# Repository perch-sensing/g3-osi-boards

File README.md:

# Perch 3GRMC Platform

## Getting Started

You'll want to clone this repo with an `ssh` key. To setup an `ssh` key on
GitHub, follow this [link](https://docs.github.com/en/github/authenticating-to-github/connecting-to-github-with-ssh).

Additionally, this README assumes that you are using Visual Studio Code.

### HW/SW

You need to initialize the various submodules with the following command:

```shell
git submodule update --init --recursive
```

The submodules include the Perch kicad library as well as micropython libraries.

### Hardware

The hardware is designed using KiCad 5.X. You will need to download KiCad from
[https://kicad.org/download/](https://kicad.org/download/).

To work with KiCad files in a Git repository, certain parts of the file should
be ignored. To ignore these commands in git, you can add to the project-local
config. To facilitate this, a `.gitconfig` file has been provided in this
repository. To use the provided `.gitconfig` file, you need to add it to the
project config.

Run the following command:

```shell
git config --local include.path ../.gitconfig
```

Next, you'll want to install `plotkicadsch` to your path. You can download
the binary [here](https://github.com/jnavila/plotkicadsch/releases). For
assistance in adding a folder to your path, visit
[this](https://www.howtogeek.com/118594/how-to-edit-your-system-path-for-easy-command-line-access/) link.

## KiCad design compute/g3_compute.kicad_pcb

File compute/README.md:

Here is a link to the Compute BOM:
https://docs.google.com/spreadsheets/d/1j4ZL0j2LjKp-IoZsxxflOpX7Q5H--Hl_RDHMVLFPHzU/edit#gid=0

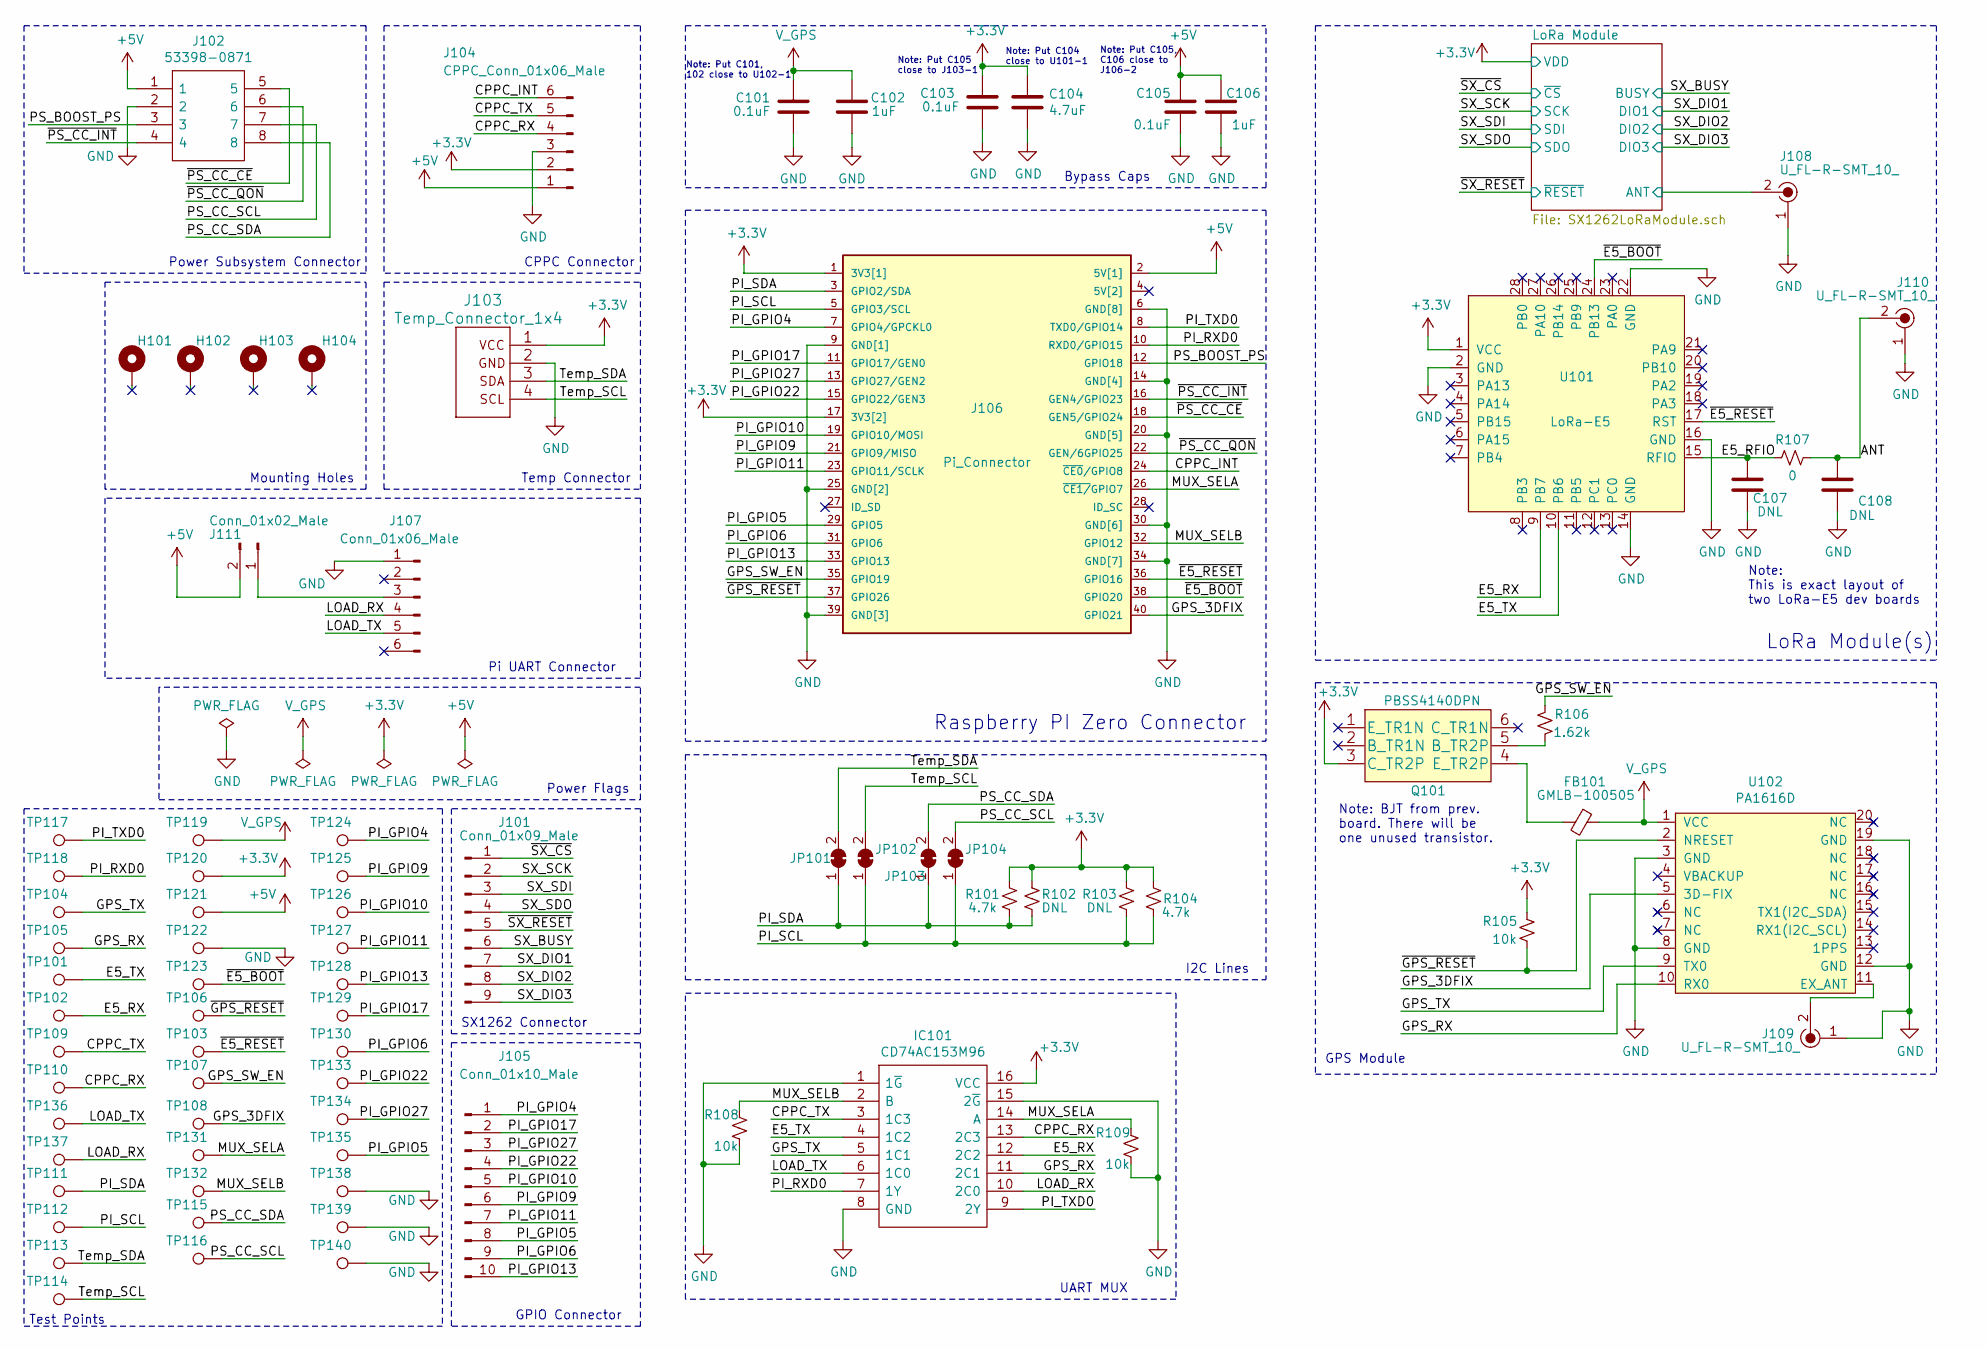
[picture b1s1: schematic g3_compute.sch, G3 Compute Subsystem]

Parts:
C101, C103, C105: 0.1uF; C_0402_1005Metric_Pad0.74x0.62mm_HandSolder
C102, C106: 1uF; C_0402_1005Metric_Pad0.74x0.62mm_HandSolder
C104: 4.7uF; C_0402_1005Metric_Pad0.74x0.62mm_HandSolder
C107, C108: DNL; C_0402_1005Metric_Pad0.74x0.62mm_HandSolder
FB101: GMLB-100505; R_0402_1005Metric_Pad0.72x0.64mm_HandSolder
H101, H102, H103, H104: MountingHole_Pad; MountingHole_2.5mm_Pad
IC101: CD74AC153M96; SOIC127P600X175-16N_MUX; Mouser Part Number 595-CD74AC153M96
J101: Conn_01x09_Male; PinHeader_1x09_P2.54mm_Vertical
J102: 53398-0871; 53398-0871_Molex
J103: Temp_Connector_1x4; 1702474_Temp_Sensor_Connector
J104: CPPC_Conn_01x06_Male; PinHeader_1x06_P2.54mm_Vertical_SMD_Pin1Left
J105: Conn_01x10_Male; PinHeader_1x10_P2.54mm_Vertical
J106: Pi_Connector; ADA3708_RaspPiZero; Manufacturer_Part_Number 2885
J107: Conn_01x06_Male; PinHeader_1x06_P2.54mm_Vertical
J108, J109, J110: U_FL-R-SMT_10_; Coax_Conn_U.FL; MPN U.FL-R-SMT(10); Digi-Key_PN H9161CT-ND
J111: Conn_01x02_Male; PinHeader_1x02_P2.54mm_Vertical_SMD_Pin1Left
JP101, JP102, JP103, JP104: SolderJumper_2_Bridged; SolderJumper-2_P1.3mm_Bridged_RoundedPad1.0x1.5mm
Q101: PBSS4140DPN
R101, R104: 4.7k; R_0402_1005Metric_Pad0.72x0.64mm_HandSolder
R102, R103: DNL; R_0402_1005Metric_Pad0.72x0.64mm_HandSolder
R105, R108, R109: 10k; R_0402_1005Metric_Pad0.72x0.64mm_HandSolder
R106: 1.62k; R_0603_1608Metric_Pad0.98x0.95mm_HandSolder
R107: 0; R_0402_1005Metric_Pad0.72x0.64mm_HandSolder
TP101, TP102, TP103, TP104, TP105, TP106, TP107, TP108, TP109, TP110, TP111, TP112, TP113, TP114, TP115, TP116, TP117, TP118, TP119, TP120, TP121, TP122, TP123, TP124, TP125, TP126, TP127, TP128, TP129, TP130, TP131, TP132, TP133, TP134, TP135, TP136, TP137, TP138, TP139, TP140: TestPoint; HARWIN_S2751-46R
U101: LoRa-E5
U102: PA1616D; PA1616D_GPS

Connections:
+3V3: C103.2, C104.1, IC101.16 (VCC), J103.1 (Vdd), J104.2, J106.1 (3V3[1]), J106.17 (3V3[2]), Q101.3 (C_TR2P), R101.2, R102.2, R103.2, R104.2, R105.2, TP120.1, U101.1 (VCC); also elsewhere on the board
+5V: C105.2, C106.2, J102.1, J104.1, J106.2 (5V[1]), J111.2, TP121.1
/ANT: C108.1, J110.2, R107.2
/CPPC_INT: J104.6, J106.24 (~CE0~/GPIO8)
/CPPC_RX: IC101.13 (2C3), J104.4, TP110.1
/CPPC_TX: IC101.3 (1C3), J104.5, TP109.1
/E5_RFIO: C107.1, R107.1, U101.15 (RFIO)
/E5_RX: IC101.12 (2C2), TP102.1, U101.9 (PB7)
/E5_TX: IC101.4 (1C2), TP101.1, U101.10 (PB6)
/GPS_3DFIX: J106.40 (GPIO21), TP108.1, U102.5 (3D-FIX)
/GPS_RX: IC101.11 (2C1), TP105.1, U102.10 (RX0)
/GPS_SW_EN: J106.35 (GPIO19), R106.2, TP107.1
/GPS_TX: IC101.5 (1C1), TP104.1, U102.9 (TX0)
/LOAD_RX: IC101.10 (2C0), J107.4, TP137.1
/LOAD_TX: IC101.6 (1C0), J107.5, TP136.1
/LoRa Module/ANT: J108.2; also elsewhere on the board
/MUX_SELA: IC101.14 (A), J106.26 (~CE1/~GPIO7), R109.2, TP131.1
/MUX_SELB: IC101.2 (B), J106.32 (GPIO12), R108.2, TP132.1
/PI_GPIO4: J105.1, J106.7 (GPIO4/GPCKL0), TP124.1
/PI_GPIO5: J105.8, J106.29 (GPIO5), TP135.1
/PI_GPIO6: J105.9, J106.31 (GPIO6), TP130.1
/PI_GPIO9: J105.6, J106.21 (GPIO9/MISO), TP125.1
/PI_GPIO10: J105.5, J106.19 (GPIO10/MOSI), TP126.1
/PI_GPIO11: J105.7, J106.23 (GPIO11/SCLK), TP127.1
/PI_GPIO13: J105.10, J106.33 (GPIO13), TP128.1
/PI_GPIO17: J105.2, J106.11 (GPIO17/GEN0), TP129.1
/PI_GPIO22: J105.4, J106.15 (GPIO22/GEN3), TP133.1
/PI_GPIO27: J105.3, J106.13 (GPIO27/GEN2), TP134.1
/PI_RXD0: IC101.7 (1Y), J106.10 (RXD0/GPIO15), TP118.1
/PI_SCL: J106.5 (GPIO3/SCL), JP102.1 (A), JP104.1 (A), R103.1, R104.1, TP112.1
/PI_SDA: J106.3 (GPIO2/SDA), JP101.1 (A), JP103.1 (A), R101.1, R102.1, TP111.1
/PI_TXD0: IC101.9 (2Y), J106.8 (TXD0/GPIO14), TP117.1
/PS_BOOST_PS: J102.3, J106.12 (GPIO18)
/PS_CC_SCL: J102.7, JP104.2 (B), TP116.1
/PS_CC_SDA: J102.8, JP103.2 (B), TP115.1
/SX_BUSY: J101.6; also elsewhere on the board
/SX_DIO1: J101.7; also elsewhere on the board
/SX_DIO2: J101.8; also elsewhere on the board
/SX_DIO3: J101.9; also elsewhere on the board
/SX_SCK: J101.2; also elsewhere on the board
/SX_SDI: J101.3; also elsewhere on the board
/SX_SDO: J101.4; also elsewhere on the board
/Temp_SCL: J103.4 (SCL), JP102.2 (B), TP114.1
/Temp_SDA: J103.3 (SDA), JP101.2 (B), TP113.1
/~E5_BOOT: J106.38 (GPIO20), TP123.1, U101.24 (PB13~)
/~E5_RESET: J106.36 (GPIO16), TP103.1, U101.17 (RST)
/~GPS_RESET: J106.37 (GPIO26), R105.1, TP106.1, U102.2 (NRESET)
/~PS_CC_CE: J102.5, J106.18 (GEN5/GPIO24)
/~PS_CC_INT: J102.4, J106.16 (GEN4/GPIO23)
/~PS_CC_QON: J102.6, J106.22 (GEN/6GPIO25)
/~SX_CS: J101.1; also elsewhere on the board
/~SX_RESET: J101.5; also elsewhere on the board
GND: C101.1, C102.1, C103.1, C104.2, C105.1, C106.1, C107.2, C108.2, IC101.1 (1~G), IC101.8 (GND), IC101.15 (2~G), J102.2, J103.2 (Gnd), J104.3, J106.6 (GND[8]), J106.9 (GND[1]), J106.14 (GND[4]), J106.20 (GND[5]), J106.25 (GND[2]), J106.30 (GND[6]), J106.34 (GND[7]), J106.39 (GND[3]), J107.1, J108.1, J109.1, J110.1, R108.1, R109.1, TP122.1, TP138.1, TP139.1, TP140.1, U101.2 (GND), U101.14 (GND), U101.16 (GND), U101.22 (GND), U102.3 (GND), U102.8 (GND), U102.12 (GND), U102.19 (GND); also elsewhere on the board
unnamed: FB101.2, Q101.4 (E_TR2P)
unnamed: J107.3, J111.1
unnamed: J109.2, U102.11 (EX_ANT)
unnamed: Q101.5 (B_TR2P), R106.1
V_GPS: C101.2, C102.2, FB101.1, TP119.1, U102.1 (VCC)

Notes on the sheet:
Power Subsystem Connector
Mounting Holes
SX1262 Connector
GPIO Connector
GPS Module
Note: BJT from prev. board. There will be one unused transistor.
Note: This is exact layout of two LoRa-E5 dev boards
Note: Put C101, 102 close to U102-1
Note: Put C105 close to J103-1
Pi UART Connector
Note: Put C105, C106 close to J106-2
Bypass Caps
Raspberry PI Zero Connector
LoRa Module(s)
Temp Connector
CPPC Connector
I2C Lines
Test Points
UART MUX
Power Flags
Note: Put C104 close to U101-1

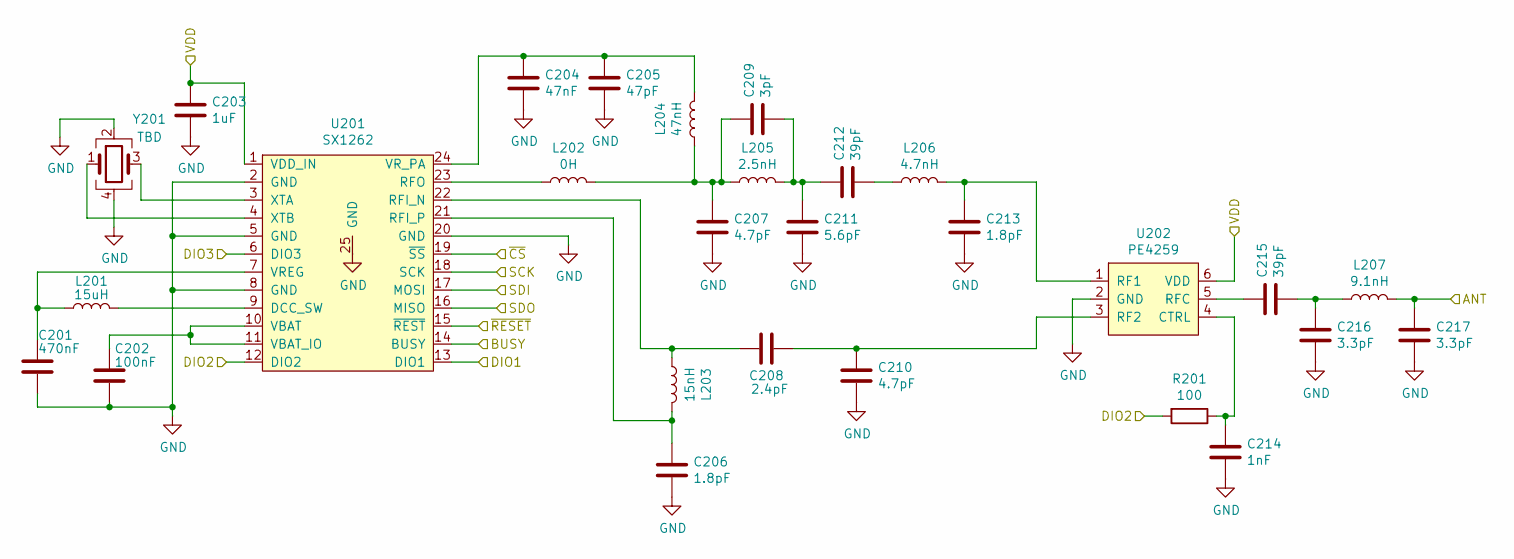
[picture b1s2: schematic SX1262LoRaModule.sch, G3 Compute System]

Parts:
C201: 470nF; C_0402_1005Metric_Pad0.74x0.62mm_HandSolder
C202: 100nF; C_0402_1005Metric_Pad0.74x0.62mm_HandSolder
C203: 1uF; C_0402_1005Metric_Pad0.74x0.62mm_HandSolder
C204: 47nF; C_0402_1005Metric_Pad0.74x0.62mm_HandSolder
C205: 47pF; C_0402_1005Metric_Pad0.74x0.62mm_HandSolder
C206, C213: 1.8pF; C_0402_1005Metric_Pad0.74x0.62mm_HandSolder
C207, C210: 4.7pF; C_0402_1005Metric_Pad0.74x0.62mm_HandSolder
C208: 2.4pF; C_0402_1005Metric_Pad0.74x0.62mm_HandSolder
C209: 3pF; C_0402_1005Metric_Pad0.74x0.62mm_HandSolder
C211: 5.6pF; C_0402_1005Metric_Pad0.74x0.62mm_HandSolder
C212, C215: 39pF; C_0402_1005Metric_Pad0.74x0.62mm_HandSolder
C214: 1nF; C_0402_1005Metric_Pad0.74x0.62mm_HandSolder
C216, C217: 3.3pF; C_0402_1005Metric_Pad0.74x0.62mm_HandSolder
L201: 15uH; L_0805_2012Metric_Pad1.05x1.20mm_HandSolder
L202: 0H; L_0402_1005Metric_Pad0.77x0.64mm_HandSolder
L203: 15nH; L_0402_1005Metric_Pad0.77x0.64mm_HandSolder
L204: 47nH; L_0402_1005Metric_Pad0.77x0.64mm_HandSolder
L205: 2.5nH; L_0402_1005Metric_Pad0.77x0.64mm_HandSolder
L206: 4.7nH; L_0402_1005Metric_Pad0.77x0.64mm_HandSolder
L207: 9.1nH; L_0402_1005Metric_Pad0.77x0.64mm_HandSolder
R201: 100; R_0402_1005Metric_Pad0.72x0.64mm_HandSolder
U201: SX1262; QFN-24-1EP_4x4mm_P0.5mm_EP2.7x2.7mm
U202: PE4259; SOT-363_SC-70-6
Y201: TBD; Crystal_SMD_2016-4Pin_2.0x1.6mm

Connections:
+3V3: C203.1, U201.1 (VDD_IN), U202.6 (VDD); also elsewhere on the board
/LoRa Module/ANT: C217.1, L207.2; also elsewhere on the board
/SX_BUSY: U201.14 (BUSY); also elsewhere on the board
/SX_DIO1: U201.13 (DIO1); also elsewhere on the board
/SX_DIO2: R201.2, U201.12 (DIO2); also elsewhere on the board
/SX_DIO3: U201.6 (DIO3); also elsewhere on the board
/SX_SCK: U201.18 (SCK); also elsewhere on the board
/SX_SDI: U201.17 (MOSI); also elsewhere on the board
/SX_SDO: U201.16 (MISO); also elsewhere on the board
/~SX_CS: U201.19 (~SS); also elsewhere on the board
/~SX_RESET: U201.15 (~REST); also elsewhere on the board
GND: C201.2, C202.2, C203.2, C204.2, C205.2, C206.2, C207.2, C210.2, C211.2, C213.2, C214.2, C216.2, C217.2, U201.2 (GND), U201.5 (GND), U201.8 (GND), U201.20 (GND), U201.25 (GND), U202.2 (GND), Y201.2, Y201.4; also elsewhere on the board
unnamed: C201.1, L201.1, U201.7 (VREG)
unnamed: C202.1, U201.10 (VBAT), U201.11 (VBAT_IO)
unnamed: C204.1, C205.1, L204.2, U201.24 (VR_PA)
unnamed: C206.1, L203.2, U201.21 (RFI_P)
unnamed: C207.1, C209.1, L202.2, L204.1, L205.1
unnamed: C208.1, L203.1, U201.22 (RFI_N)
unnamed: C208.2, C210.1, U202.3 (RF2)
unnamed: C209.2, C211.1, C212.1, L205.2
unnamed: C212.2, L206.1
unnamed: C213.1, L206.2, U202.1 (RF1)
unnamed: C214.1, R201.1, U202.4 (CTRL)
unnamed: C215.1, U202.5 (RFC)
unnamed: C215.2, C216.1, L207.1
unnamed: L201.2, U201.9 (DCC_SW)
unnamed: L202.1, U201.23 (RFO)
unnamed: U201.3 (XTA), Y201.3
unnamed: U201.4 (XTB), Y201.1

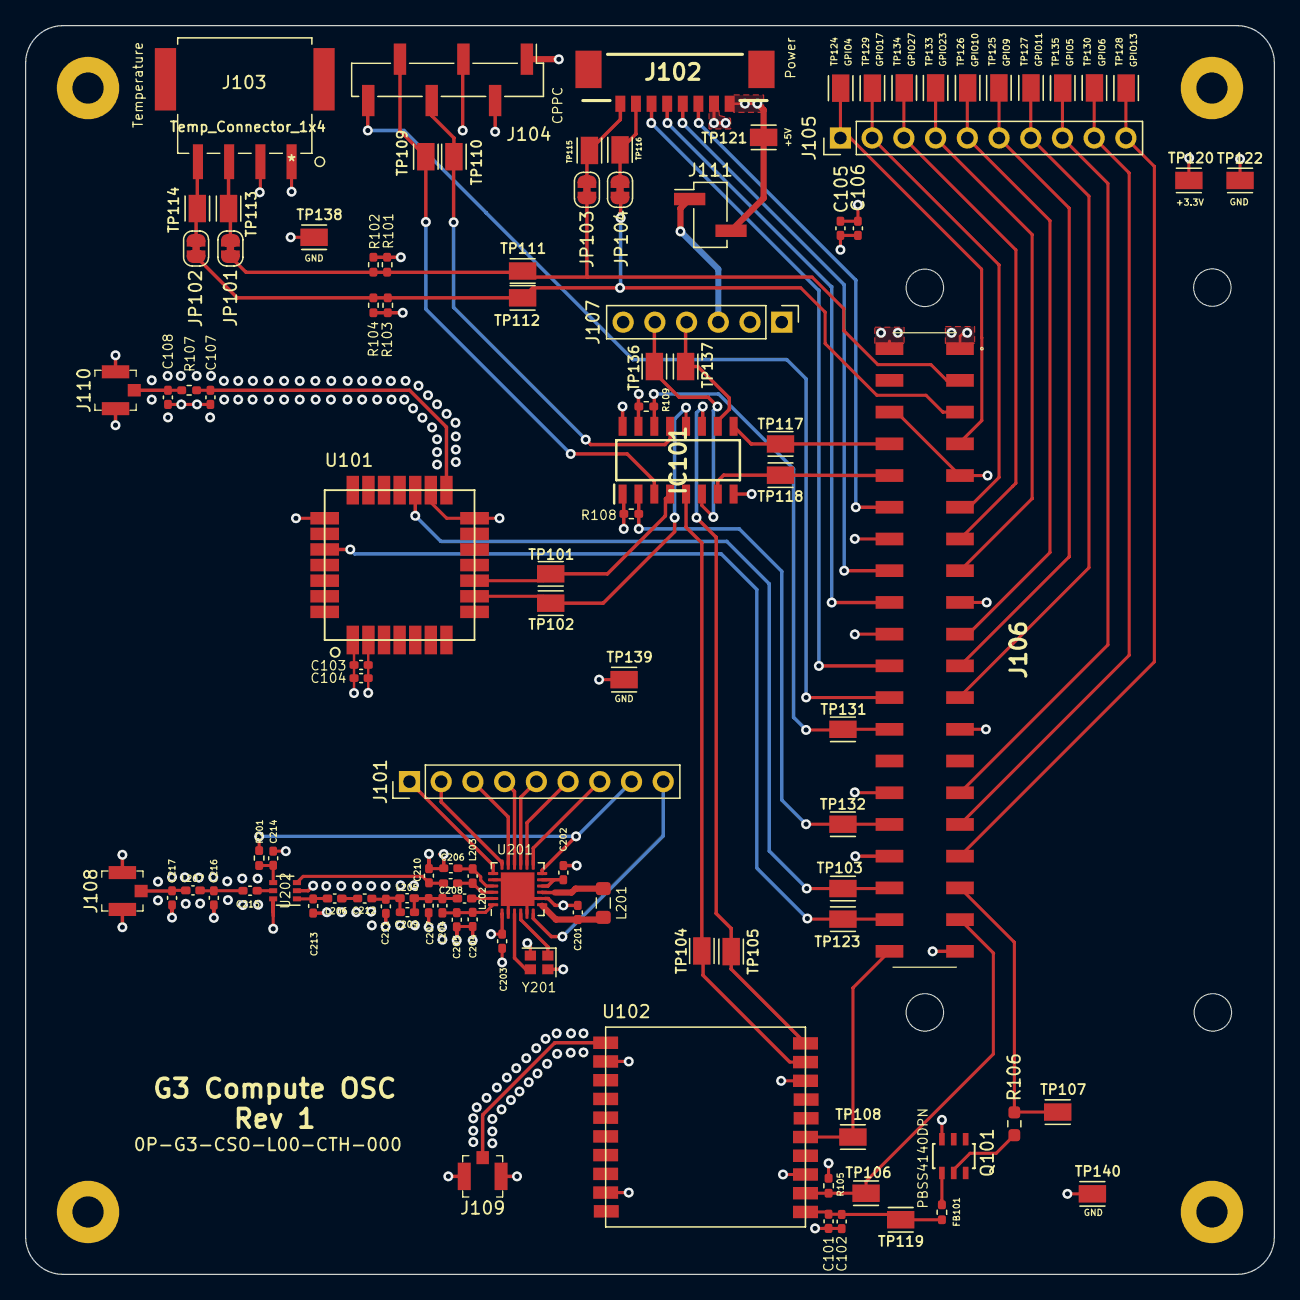
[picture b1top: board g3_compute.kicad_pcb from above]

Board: 4 copper layers, 100.0 x 100.0 mm, 109 parts (0 on the bottom side), 75 nets.

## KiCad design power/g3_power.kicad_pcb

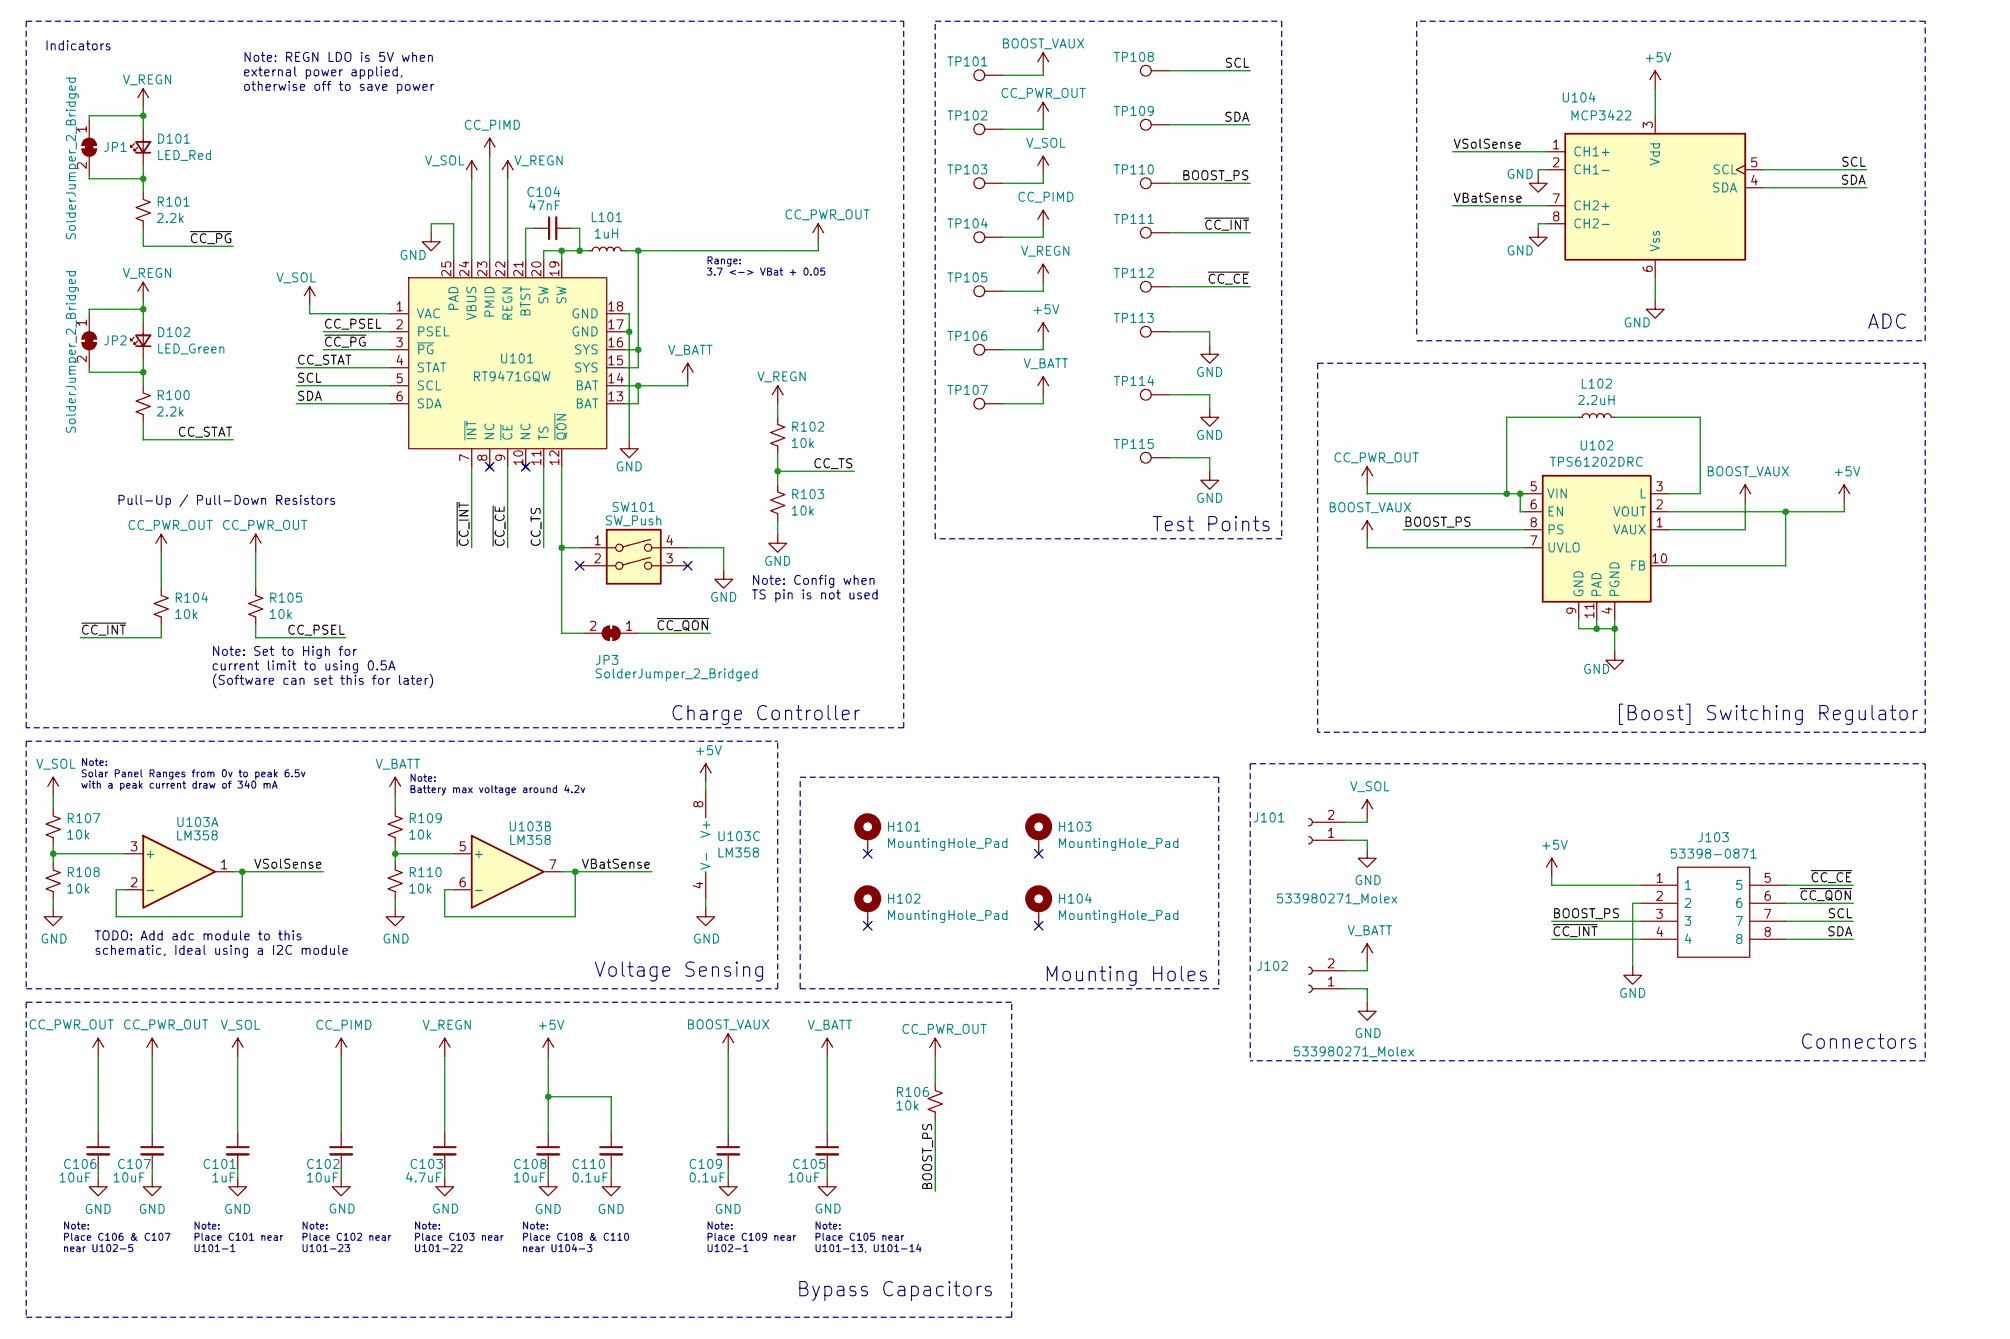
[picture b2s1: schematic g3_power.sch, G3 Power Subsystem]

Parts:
C101: 1uF; C_0402_1005Metric_Pad0.74x0.62mm_HandSolder; Manufacturer_Part_Number CC0402MRX5R6BB105
C102, C105, C106, C107, C108: 10uF; C_0402_1005Metric_Pad0.74x0.62mm_HandSolder; Manufacturer_Part_Number CAP CER 10000PF 16V X7R 0402
C103: 4.7uF; C_0402_1005Metric_Pad0.74x0.62mm_HandSolder; Manufacturer_Part_Number CC0402MRX5R6BB475
C104: 47nF; C_0805_2012Metric_Pad1.18x1.45mm_HandSolder; Manufacturer_Part_Number CL21B473KCCWPNC
C109, C110: 0.1uF; C_0402_1005Metric_Pad0.74x0.62mm_HandSolder; Manufacturer_Part_Number CC0402JRX7R7BB104
D101: LED_Red; LED_0402_1005Metric_Pad0.77x0.64mm_HandSolder; Manufacturer_Part_Number SML-LX0402SIC-TR
D102: LED_Green; LED_0402_1005Metric_Pad0.77x0.64mm_HandSolder; Manufacturer_Part_Number SML-LX0402SUGC-TR
H101, H102, H103, H104: MountingHole_Pad; MountingHole_2.5mm_Pad
J101, J102: 533980271_Molex; 532610271_Molex; Manufacturer_Part_Number 532610271
J103: 53398-0871; 53398-0871_Molex; Mouser Part Number 538-53398-0871
JP1, JP2, JP3: SolderJumper_2_Bridged; SolderJumper-2_P1.3mm_Bridged_RoundedPad1.0x1.5mm
L101: 1uH; L_1008_2520Metric_Pad1.43x2.20mm_HandSolder; Manufacturer_Part_Number CIGT252010LM1R0MNE
L102: 2.2uH; L_0805_2012Metric_Pad1.15x1.40mm_HandSolder; Manufacturer_Part_Number CIGT201610LH2R2MNE
R100, R101: 2.2k; R_0402_1005Metric_Pad0.72x0.64mm_HandSolder; Manufacturer_Part_Number RC0402JR-072K2L
R102, R103, R104, R105, R106, R107, R108, R109, R110: 10k; R_0402_1005Metric_Pad0.72x0.64mm_HandSolder; Manufacturer_Part_Number RC0402JR-0710KL
SW101: SW_Push; Switch_Tactile_SMD_6x6mm_PTS645; Manufacturer_Part_Number PTS645SH43SMTR92 LFS
TP101, TP102, TP103, TP104, TP105, TP106, TP107, TP108, TP109, TP110, TP111, TP112, TP113, TP114, TP115: TestPoint; HARWIN_S2751-46R
U101: RT9471GQW; WQFN-24-1EP_4x4mm_P0.5mm_EP2.6x2.6mm_ThermalVias; Manufacturer_Part_Number RT9471GQW(2)
U102: TPS61202DRC; VSON-10-1EP_3x3mm; Manufacturer_Part_Number TPS61202DRCT
U103: LM358; SOIC-8_3.9x4.9mm_P1.27mm; Manufacturer_Part_Number LM358D
U104: MCP3422; SOIC-8_3.9x4.9mm_P1.27mm; Manufacturer_Part_Number MCP3422A1T-E/SN

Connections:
+5V: C108.1, C110.1, J103.1, TP106.1, U102.2 (VOUT), U102.10 (FB), U103.8 (V+), U104.3 (Vdd)
/BOOST_PS: J103.3, R106.2, TP110.1, U102.8 (PS)
/CC_PSEL: R105.2, U101.2 (PSEL)
/CC_STAT: R100.2, U101.4 (STAT)
/CC_TS: R102.2, R103.1, U101.11 (TS)
/SCL: J103.7, TP108.1, U101.5 (SCL), U104.5 (SCL)
/SDA: J103.8, TP109.1, U101.6 (SDA), U104.4 (SDA)
/VBatSense: U103.6 (-), U103.7, U104.7 (CH2+)
/VSolSense: U103.1, U103.2 (-), U104.1 (CH1+)
/~CC_CE: J103.5, TP112.1, U101.9 (~CE)
/~CC_INT: J103.4, R104.2, TP111.1, U101.7 (~INT)
/~CC_PG: R101.2, U101.3 (~PG)
/~CC_QON: J103.6, JP3.1 (A)
BOOST_VAUX: C109.1, TP101.1, U102.1 (VAUX), U102.7 (UVLO)
CC_PIMD: C102.1, TP104.1, U101.23 (PMID)
CC_PWR_OUT: C106.1, C107.1, L101.2, L102.1, R104.1, R105.1, R106.1, TP102.1, U101.15 (SYS), U101.16 (SYS), U102.5 (VIN), U102.6 (EN)
GND: C101.2, C102.2, C103.2, C105.2, C106.2, C107.2, C108.2, C109.2, C110.2, J101.1, J102.1, J103.2, R103.2, R108.2, R110.2, SW101.4, TP113.1, TP114.1, TP115.1, U101.17 (GND), U101.18 (GND), U101.25 (PAD), U102.4 (PGND), U102.9 (GND), U102.11 (PAD), U103.4 (V-), U104.2 (CH1-), U104.6 (Vss), U104.8 (CH2-)
unnamed: C104.1, U101.21 (BTST)
unnamed: C104.2, L101.1, U101.19 (SW), U101.20 (SW)
unnamed: D101.1 (K), JP1.2 (B), R101.1
unnamed: D102.1 (K), JP2.2 (B), R100.1
unnamed: JP3.2 (B), SW101.1, U101.12 (~QON)
unnamed: L102.2, U102.3 (L)
unnamed: R107.2, R108.1, U103.3 (+)
unnamed: R109.2, R110.1, U103.5 (+)
V_BATT: C105.1, J102.2, R109.1, TP107.1, U101.13 (BAT), U101.14 (BAT)
V_REGN: C103.1, D101.2 (A), D102.2 (A), JP1.1 (A), JP2.1 (A), R102.1, TP105.1, U101.22 (REGN)
V_SOL: C101.1, J101.2, R107.1, TP103.1, U101.1 (VAC), U101.24 (VBUS)

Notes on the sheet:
Connectors
[Boost] Switching Regulator
Note: Solar Panel Ranges from 0v to peak 6.5v with a peak current draw of 340 mA
Voltage Sensing
Note: Battery max voltage around 4.2v
TODO: Add adc module to this schematic, Ideal using a I2C module
Note: Set to High for current limit to using 0.5A (Software can set this for later)
Note: REGN LDO is 5V when external power applied, otherwise off to save power
Range: 3.7 <-> VBat + 0.05
Pull-Up / Pull-Down Resistors
Indicators
ADC
Note: Place C106 & C107 near U102-5
Note: Place C109 near U102-1
Note: Place C105 near U101-13, U101-14
Note: Place C108 & C110 near U104-3
Charge Controller
Note: Place C102 near U101-23
Note: Place C101 near U101-1
Note: Place C103 near U101-22
Bypass Capacitors
Note: Config when TS pin is not used
Mounting Holes
Test Points

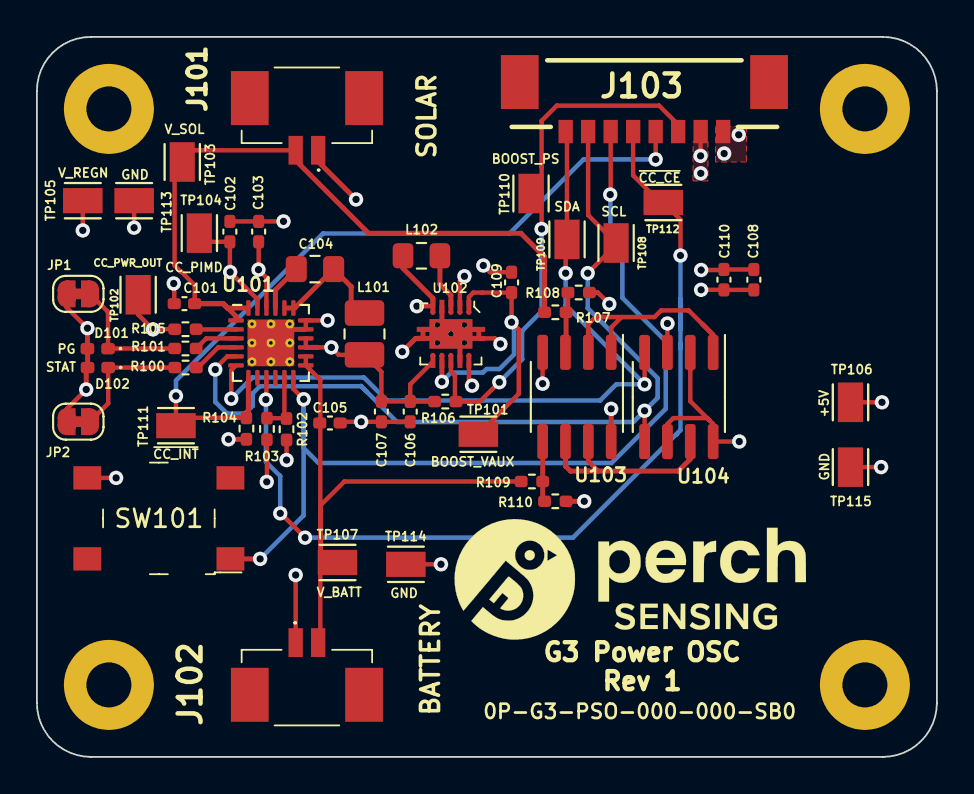
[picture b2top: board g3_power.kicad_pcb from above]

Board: 4 copper layers, 50.0 x 40.0 mm, 55 parts (1 on the bottom side), 28 nets.

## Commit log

2021-10-02 add initial project files
2021-11-10 Adding LoRa module
2021-11-12 Updating submodule head
2021-11-15 added GPS and Raspberry Pi Zero symbols to symbol editor
2021-11-15 added GPS and PI to schematic
2021-11-15 added temp sensor symbol
2021-11-15 added temp sensor to schematic
2021-11-15 Testing collisions
2021-11-15 temp sensor connector footprint
2021-11-17 Adding LoRa-E5 library
2021-11-17 test - added LoRa to sch
2021-11-21 Updating schematic and began routing LoRa module
2021-11-21 Finish LoRa routing
2021-11-22 small changes
2021-11-22 some small changes
2021-11-22 Added interfacing to GPS Module
2021-11-22 added Temp connector interfacing
2021-11-22 added some connections from PI to LoRa module
2021-11-24 added extra field values to modules in schematic to help with BOM managment
2021-11-26 changed up wiring in schematic
2021-11-26 updated GPS module
2021-11-29 Fixing libraries and schematic ref nums
2021-11-29 added temperature sensor interfacing and changed page layout path
2021-11-30 Wiring pi pins to modules
2021-12-01 added appropriate custom fields to GPS, MPU, and Temp connector for BOM use
2021-12-01 added appropriate custom fields to GPS, MPU, and Temp connector for BOM usage
2021-12-03 added 470ohm resistors fields to BOM
2021-12-03 Added fields for 4.7uF and 470nF capacitors
2021-12-03 added 47nF and 100nF capacitor fields
2021-12-15 added charge controller and switching regulator symbols to schematic
2021-12-15 added interfacing to charge controller on schematic
2021-12-15 added VR interfacing on schematic
2021-12-15 small changes to VR interfacing
2021-12-15 added fields for power BOM
2021-12-15 update on BOM
2021-12-22 added fields to power BOM
2021-12-22 small changes to power schematic layout
2021-12-22 referenced charge controller footprint in schematic
2021-12-22 updated compute schematic with test points and UART connections
2021-12-22 added remaining GPIO on PI to a header
2021-12-22 rework on sch and layout
2021-12-22 Mering in LoRa BOM field changes
2021-12-22 BOM fields changes to LoRa module
2021-12-22 Adding Power Subsystem connector
2021-12-23 test points, footprints fixes, and layout fixes
2021-12-26 Finishing Charge Controller Implementation
2021-12-28 Updating Power subsystem BOM fields and board to board connector
2022-01-05 Adding Power to compute connector
2022-01-05 Adjusting board connectors
2022-01-05 Adjusting connectors foot prints
2022-01-05 First preliminary layout of pcb
2022-01-10 Mapping Power systems signals to pi
2022-01-10 changes to compute
2022-01-11 fixes to power and compute
2022-01-11 adding footprints
2022-01-11 added footprints
2022-01-11 Making changes suggested
2022-01-11 Updated BOM on compute subsystem
2022-01-11 some more updates to compute BOM
2022-01-11 Changed connectors symbols to be molex connectors
2022-01-11 Some small updates to molex symbols
2022-01-12 Added 2 pin molex connector symbol and footprints
2022-01-12 Removed GPS_Switch sheet, changed symbol for all resistors on compute schematic
2022-01-12 Major changes to Power sch
2022-01-12 Various changes to compute schematic given by Perch feedback
2022-01-13 More changes to compute schematic given by perch feedback
2022-01-14 several more changes to compute schematic
2022-01-14 added new VR
2022-01-14 Added new connector for Pi UART
2022-01-15 Annotated schematic and updated field values
2022-01-15 Added test points for both I2C wires
2022-01-15 final touches to second revision
2022-01-15 Changed page revision from 1 to 2
2022-01-15 Added the backup LoRa module again
2022-01-19 adding ADC and old VR
2022-01-20 added some minor changes according to Perch feedback
2022-01-20 Made NC pins more consistent on compute schematic
2022-01-21 Removed UART Resitors, Fixed I2C pull up resistors, changed Pi UART Connector to standard male header
2022-01-21 Added switch to compute schematic
2022-01-21 Added to kicad-lib
2022-01-21 Changes to kicad-lib
2022-01-21 Changed out the two molex connectors to what is wanted in the feedback
2022-01-21 Added mounting holes
2022-01-22 changes to power symbols and bypass caps
2022-01-23 changed BJT to PBSS4140DPN symbol
2022-01-23 Sized BJT switch transistor
2022-01-23 Added SX1262 pins to a breakout
2022-01-23 Sized LoRa RF caps and inductors
2022-01-23 Changed to revision 3
2022-01-23 Added all pins to SX1262 connector
2022-01-27 Changed to revision 4 and made I2C pullup resisotrs 4.7k
2022-01-27 Added E5s PB13 pin as E5_BOOT and connected it to a GPIO, also changed the GPIO header to 6 pins instead of 7
2022-01-27 Updates to kicad-lib
2022-01-27 Moved schematic around to make room for mux, also placed mux
2022-01-27 Wired up the mux with UART pins
2022-01-27 Fix GPIO connector
2022-01-27 Added power flags
2022-01-28 Updated BOM
2022-01-28 Changed Pi connector footprint
2022-01-28 Started compute board layout
2022-01-28 Changed notes on compute schematic
2022-01-28 made changes and layout
2022-01-31 Moved all parts around for PCB layout except second LoRa module
2022-02-02 Changed TP footprint to new footprint
2022-02-02 Changed pinout to GPIO Connector to make routing easier
2022-02-02 Changed pinnout of UART MUX to make routing easier
2022-02-02 Changed Pi footprint
2022-02-02 Routed GPIO connector to Pi
2022-02-02 Started I2C routing
2022-02-02 Routed all of the connectors except for backup LoRa
2022-02-02 Finished routing all modules except second LoRa
2022-02-02 Filled all zones for power and ground planes
2022-02-03 First alternative revision
2022-02-03 Finishing GPIO header wiring
2022-02-04 Adding more GND testpoints
2022-02-04 Revert "Adding more GND testpoints"
    This reverts commit 458bd6481f51bde2da150f265f3cf5d6fabf7a4a.
2022-02-04 Adding more testpoints, without breaking things
2022-02-04 Matching GND paths from Power Subsystem
2022-02-04 Revisioning, rev 1
2022-02-04 Adding waveguides and note to compute RF signals
2022-02-04 Added README in compute folder with link to BOM
2022-02-08 Making suggested changes
2022-02-08 Changing +5v power supply from UART LOADER
2022-02-08 Changed Pi Connectors field values and added more values to two pin connector
2022-02-08 fixes to schematic and layout
2022-02-08 Clearing old pcb file
2022-02-08 Rerouting power PCB
2022-02-08 Clearing up reference designators
2022-02-09 Labeling testpoints
2022-02-09 Adding logo
2022-02-09 Renaming boards
2022-02-10 Making review 2 changes
2022-02-10 added part numbers
2022-02-10 Fixing fab layers and stray trace
2022-02-10 Adding board part number
2022-02-15 U.FL replacement as well as CPPC connector
2022-02-15 Fixing exclude regions
2022-02-16 Generating gerbers
2022-03-15 Flipped GPS switch to use PNP BJT
2022-05-14 Updating selected UART mux part
2022-05-14 Reupdating UART mux

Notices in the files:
parts and their libraries:
Copyright 2016 Accelerated Designs. All rights reserved.
